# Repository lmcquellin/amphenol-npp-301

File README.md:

# Use of Amphenol NPP-301 Series Pressure Transducers for Pressure Measurements

## 1. Overview
The NPP-301 series of pressure sensors manufactured by Amphenol Advanced Sensors have demonstrated to be a low cost means of collecting discrete pressure measurements in space constrained locations on wind tunnel models. The transducer is offered in three pressure ranges, 0 – 100 kPa, 0 - 200 kPa, and 0 – 700 kPa.

## 2. Electrical Characteristics

Figure 1 presents the electrical schematic of the NPP-301 as supplied by Amphenol. The large variation in transducer input and output impedance (20% [1]) results in a large amount of transducer-to-transducer variation. Additionally, because the operating pressure can be an order of magnitude lower than the rated pressure, the transducer is having to operate at the extremity of its operating range. The split negative input pins (Pins 4 & 5) allow for the bridge to be compensated through the use of an additional resistor. This compensation allows for the bridge to be balanced at a desired pressure. This has two effects. First, the balanced bridge means that the bridge output voltage is minimised, allowing for greater amplifier dynamic range. Secondly, the bridge compensation process reduces the large variation in transducer output performance between sensors, allowing for simpler amplifiers to be used.

## 3. Frequency Response

Frequency response has not been characterised, but is estimated to be on the order of several kilohertz.

## 4. Bridge Compensation

Bridge compensation is performed using a vacuum cell with a 5 wire feed-through, a mounting PCB or carrier board for connecting to the sensor and a digital multimeter. Details of calibration carrier boards are provided in appendix A.

Bridge compensation is performed as follows:
* If not mounted to a PCB, transducer body is marked for identification. If mounted to a PCB, PCB is typically marked. Transducer is then placed in the integrated circuit socket.
* Mounting PCB or test socket is interconnected through the vacuum cell feed-through, with 5 flying-lead wires available externally for measurement connections.
* Vacuum cell is evacuated to the desired compensation pressure. This is typically $\<$ 100 Pa for wind tunnel testing with evacuated test sectionbs. Ambient temperature during the calibration should also be recorded.
* The following resistances are then measured between pin pairs on the transducer body, using externally available wires. Pin 8 & 2, Pin 8 & 6, Pin 2 & 4, and Pin 6 & 5. Resistance values will typically be in the 4500 - 4900 Ω range and should be recorded to the nearest ohm.

This procedure is repeated for each transducer with the results being populated in a text file called 'resistor_data.txt'. File should be TAB delimited. The resistor_data text file takes the following format:
'''
PIN 8/2  PIN 8/6	PIN 2/4	PIN 6/5
'''

Again, resistance of each measurement element should be recorded in ohms to the nearest ohm. An example have been provided in 'resistor_data.txt'. Once complete, the compensation values for each individual transducer can be determined. To do this, the MATLAB script 'npp_comp.m' is used. Note: 'npp_comp.m' requires 'resval.mat' in order to run successfully. 'resval.mat' is also provided as a comma-separated values file. The script, when run, will evaluate all resistance values present in the 'resistor_data.txt' data file. For each transducer, a suggested compensation resistor value will be provided based on commercially available resistance values (contained in 'resval.mat'), and the branch of the wheatstone bridge this resistance should be provided. The script will also provide a bridge output voltage (Vb) for a given bridge input voltage at the compensated pressure. It is advised that the reported resistance is then recorded in a transducer calibration register (see 'npp_calibration_register_blank.ods') as this will be cleared from the screen when the script is run again. The following provides an example of the script output for a transducer with the values PIN 8/2 = 4726, PIN 8/6 = 4752 PIN 2/4 = 4769 PIN 6/5 = 4742.

```
------
OUTPUT
------
Input Voltage: 5V
Suggested Compensation Resistance: 51 Ohms
Compensation on Leg: 865
Vb: 0.58314 mV
```
Figure 3 presents a revised schematic that includes the compensation resistor and its position within the circuit. It can be seen that the compensation resistor is connected between pins 4 & 5, with the IN- connection point becoming pin 4. Depending on the mounting configuration, the means in which this resistor can be included into the pressure transducer can vary. Two methods are presented here, PCB mounting (subsection 5.1) and ’deadbug’ mounting (subsection 5.2).

## 5. Packaging and Mounting

The NPP-301 is available in a small-outline 8 (SO8) surface mount package with either a barbless (NPP-301A) or barbed (NPP-301B) pressure port [1]. Dimensions of the barbed and barbless packaging are
available in appendix A. Two mounting options have been explored thus far. Printed circuit board (PCB) mounting and ‘deadbug’ mounting.

### 5.1 PCB Mounting

PCB mounting allows for a transducer to be rigidly mounted to a structure with fasteners. Multiple transducers can also be mounted to a single PCB to simplify interconnectivity and maximise measurement density. The SO8 package size and placement of the barb limits the pitch of an array of transducers to 8 mm. An example of a transducer mounted to a single PCB is provided in Fig. 4. This arrangement where the transducer body is offset from the horizontal centreline of the PCB is done so to place the barb in the horizontal and vertical centre of the board. Four mounting holes suitable for M1.6 fasteners are used in each corner. On the reverse side of the PCB; pads for soldered wire connections are provided, along with pads for surface mount 0402 size compensation resistors. To ensure a adequate pressure connection between the pressure port of the sensor and the pressure tap on the surface of the model, a BS003 o-ring is used to provide a seal. Geometry for the o-ring groove is provided in appendix B. Typical dimensions of a single transducer mounting PCB is also provided in appendix B.

### 5.2 Deadbug Mounting

Deadbug mounting, named due to the appearance of an integrated circuit package body upside down, is the other proposed method for interconnecting and mounting the transducer. This mounting type is the most volumetrically efficient, but is more time consuming the manufacture and mounting into a model is permanent. Instructions to assembly a transducer body with wire is provided in appendix C. Transducer bodies are typically bonded into cavities or against panels using epoxy (or other suitable) adhesive. This is depicted in Fig. 5. When using the barbless ‘A’ package, ensuring concentricity between the pressure tap in the panel and port in the transducer can be achieved by using a machined locating pin to locate the transducer during assembly. When using the barbed ‘B’ package, a countersink in the surface is required to accommodate the barb. This countersink ensures port concentricity during mating.

## References

[1] Amphenol Advanced Sensors. NPP-301 Series Surface Mount Pressure Sensor, 3 2019. web: https://www.amphenol-sensors.com/hubfs/Documents/AAS-920-297B-NovaSensor-NPP-301-031414-web.pdf

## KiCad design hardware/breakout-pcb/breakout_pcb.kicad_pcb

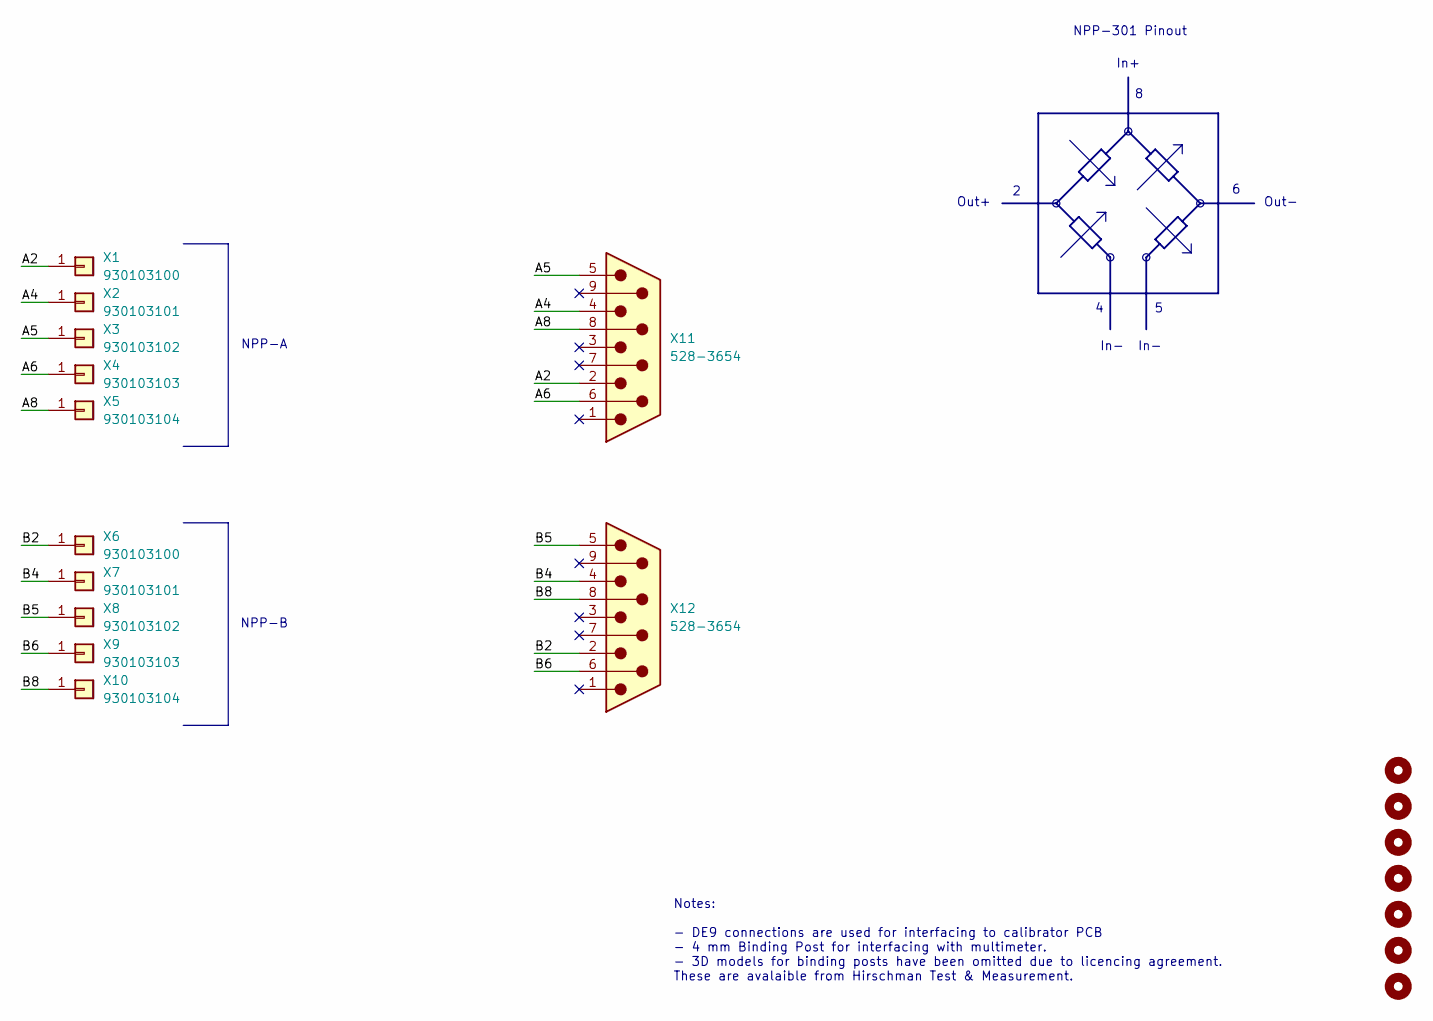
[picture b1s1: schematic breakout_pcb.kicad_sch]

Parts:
H1, H2, H3, H4, H5, H6, H7: M3; MountingHole_3.2mm_M3_ISO7380_Pad
X1, X6: 930103100; MountingHole_4.3mm_M4_DIN965_Pad
X2, X7: 930103101; MountingHole_4.3mm_M4_DIN965_Pad
X3, X8: 930103102; MountingHole_4.3mm_M4_DIN965_Pad
X4, X9: 930103103; MountingHole_4.3mm_M4_DIN965_Pad
X5, X10: 930103104; MountingHole_4.3mm_M4_DIN965_Pad
X11, X12: 528-3654; DSUB-9_Male_Horizontal_P2.77x2.84mm_EdgePinOffset9.40mm

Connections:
/A2: X1.1, X11.2
/A4: X2.1, X11.4
/A5: X3.1, X11.5
/A6: X4.1, X11.6
/A8: X5.1, X11.8
/B2: X6.1, X12.2
/B4: X7.1, X12.4
/B5: X8.1, X12.5
/B6: X9.1, X12.6
/B8: X10.1, X12.8

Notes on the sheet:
Notes: - DE9 connections are used for interfacing to calibrator PCB - 4 mm Binding Post for interfacing with multimeter. - 3D models for binding posts have been omitted due to licencing agreement. These are avalaible from Hirschman Test & Measurement.
In+
In-
NPP-301 Pinout
NPP-B
Out-
Out+
NPP-A

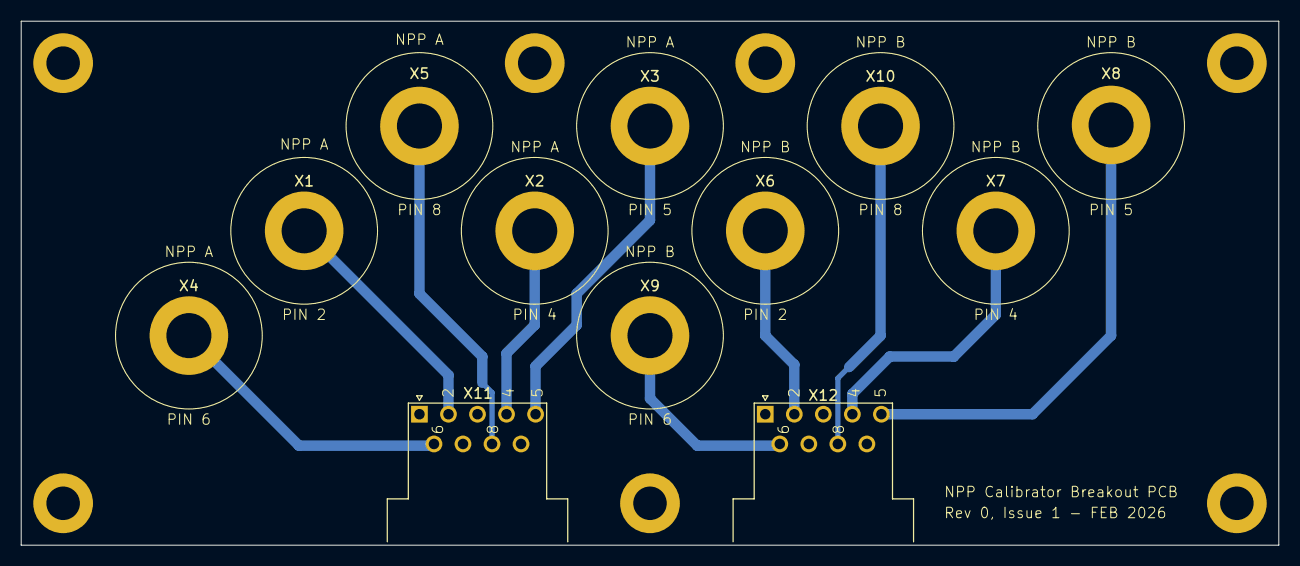
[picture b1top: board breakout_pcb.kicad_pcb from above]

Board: 2 copper layers, 120.0 x 50.0 mm, 19 parts (0 on the bottom side), 10 nets.

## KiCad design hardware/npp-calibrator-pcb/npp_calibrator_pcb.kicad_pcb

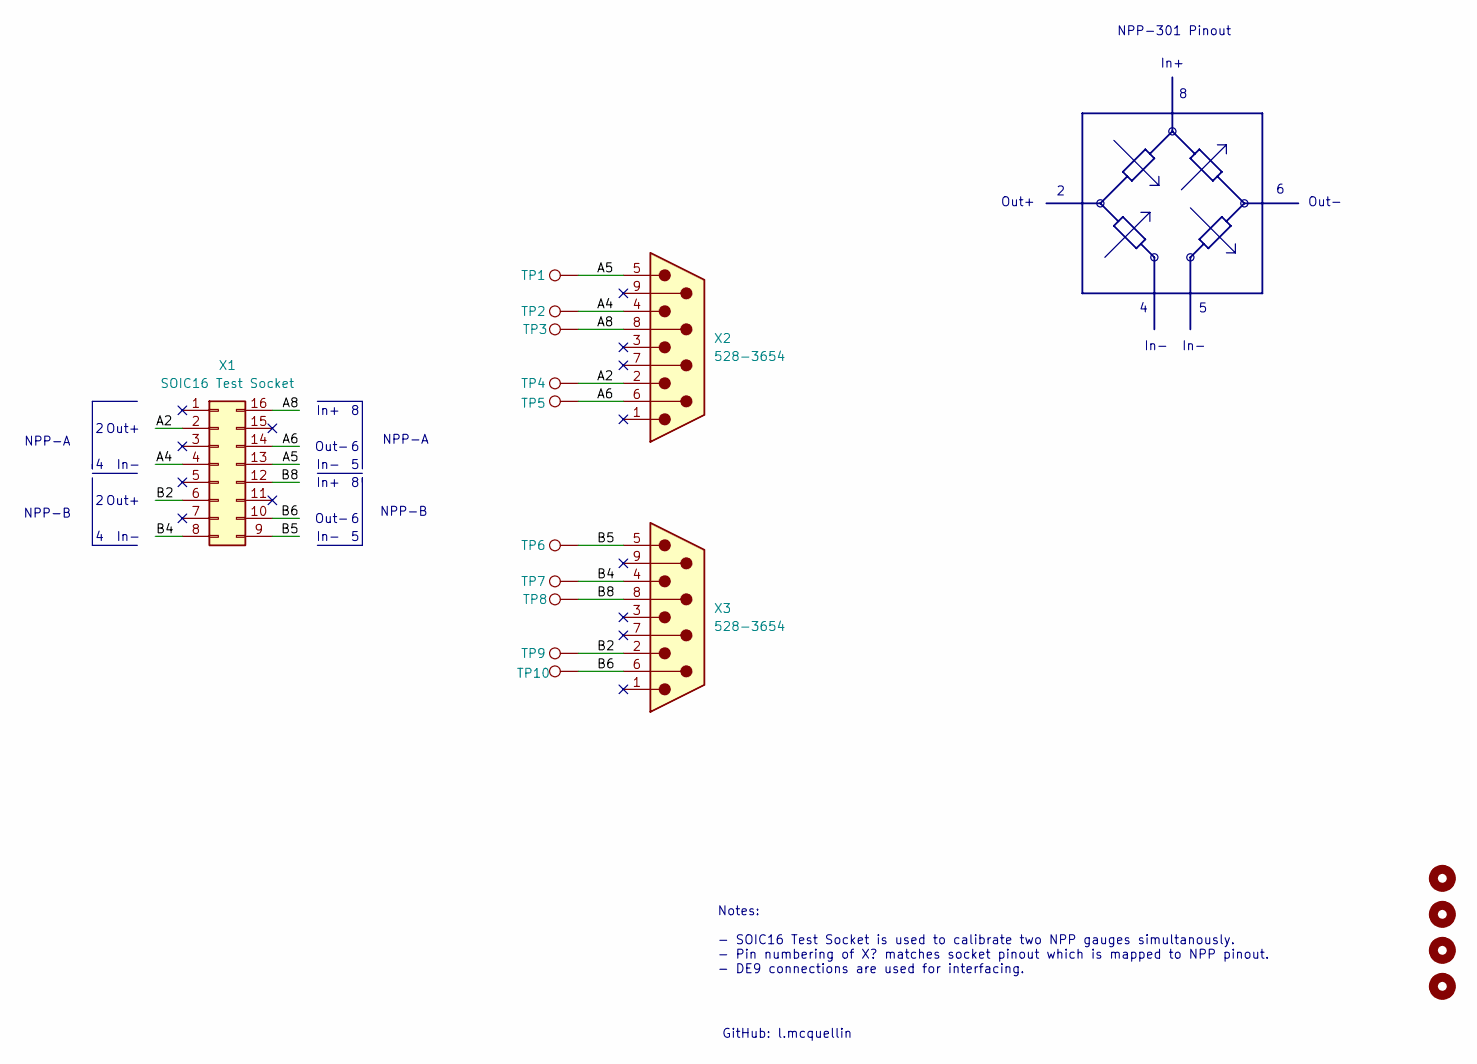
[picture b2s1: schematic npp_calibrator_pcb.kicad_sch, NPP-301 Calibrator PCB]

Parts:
H1, H2, H3, H4: M3; MountingHole_3.2mm_M3_ISO7380_Pad
TP1, TP2, TP3, TP4, TP5, TP6, TP7, TP8, TP9, TP10: TestPoint; TestPoint_Pad_D2.0mm
X1: SOIC16 Test Socket; PA-SOCKET-SOICN-16-1.27
X2, X3: 528-3654; DSUB-9_Male_Horizontal_P2.77x2.84mm_EdgePinOffset9.40mm

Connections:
/A2: TP4.1, X1.2, X2.2
/A4: TP2.1, X1.4, X2.4
/A5: TP1.1, X1.13, X2.5
/A6: TP5.1, X1.14, X2.6
/A8: TP3.1, X1.16, X2.8
/B2: TP9.1, X1.6, X3.2
/B4: TP7.1, X1.8, X3.4
/B5: TP6.1, X1.9, X3.5
/B6: TP10.1, X1.10, X3.6
/B8: TP8.1, X1.12, X3.8

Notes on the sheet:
In-
NPP-B
In+
NPP-A
Out-
Notes: - SOIC16 Test Socket is used to calibrate two NPP gauges simultanously. - Pin numbering of X? matches socket pinout which is mapped to NPP pinout. - DE9 connections are used for interfacing.
Out+
NPP-301 Pinout
GitHub: l.mcquellin

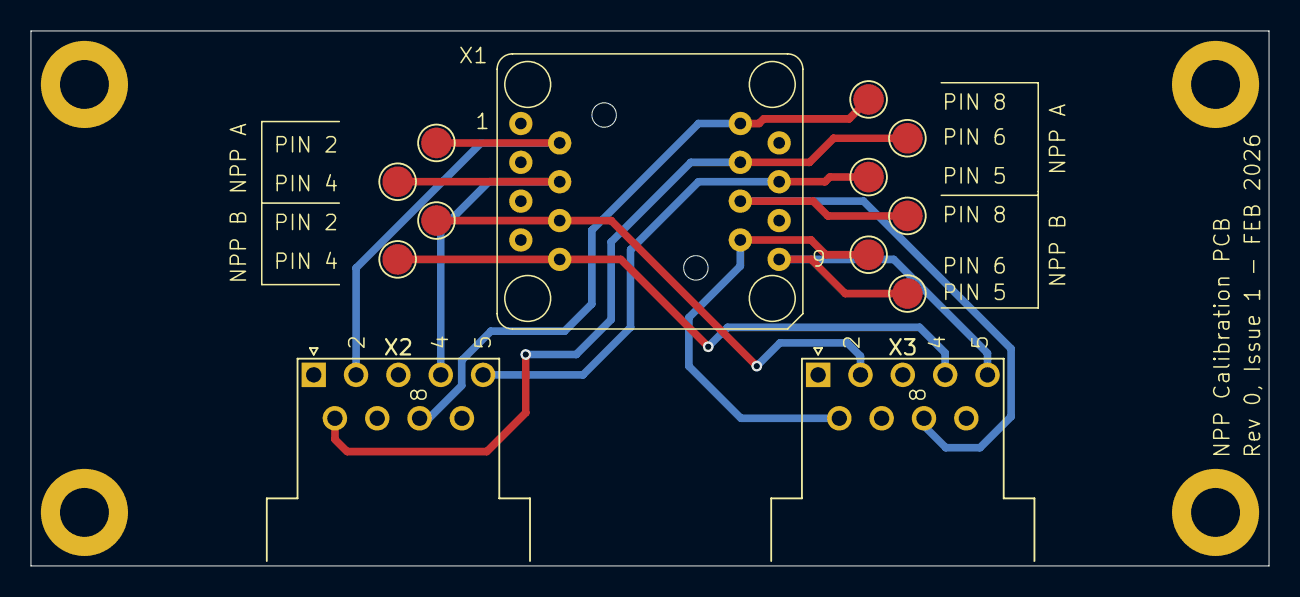
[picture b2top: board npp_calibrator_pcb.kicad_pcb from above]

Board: 2 copper layers, 81.0 x 35.0 mm, 17 parts (0 on the bottom side), 10 nets.

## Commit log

2023-07-08 Commit of draft readme, associated images and sensor 3d models.
    Draft README, images supporting readme and 3d models of the sensors in .STEP format.
2023-07-08 Adding calibration register and figures for readme.
2023-07-08 Added PNG figures to support readme
2023-07-08 PNG exports from SVG files
2024-06-06 Deleted duplicate file
2025-11-26 add calibrator pcb design files
2026-02-24 Updates to calibration hardware
2026-02-24 Hardware update
